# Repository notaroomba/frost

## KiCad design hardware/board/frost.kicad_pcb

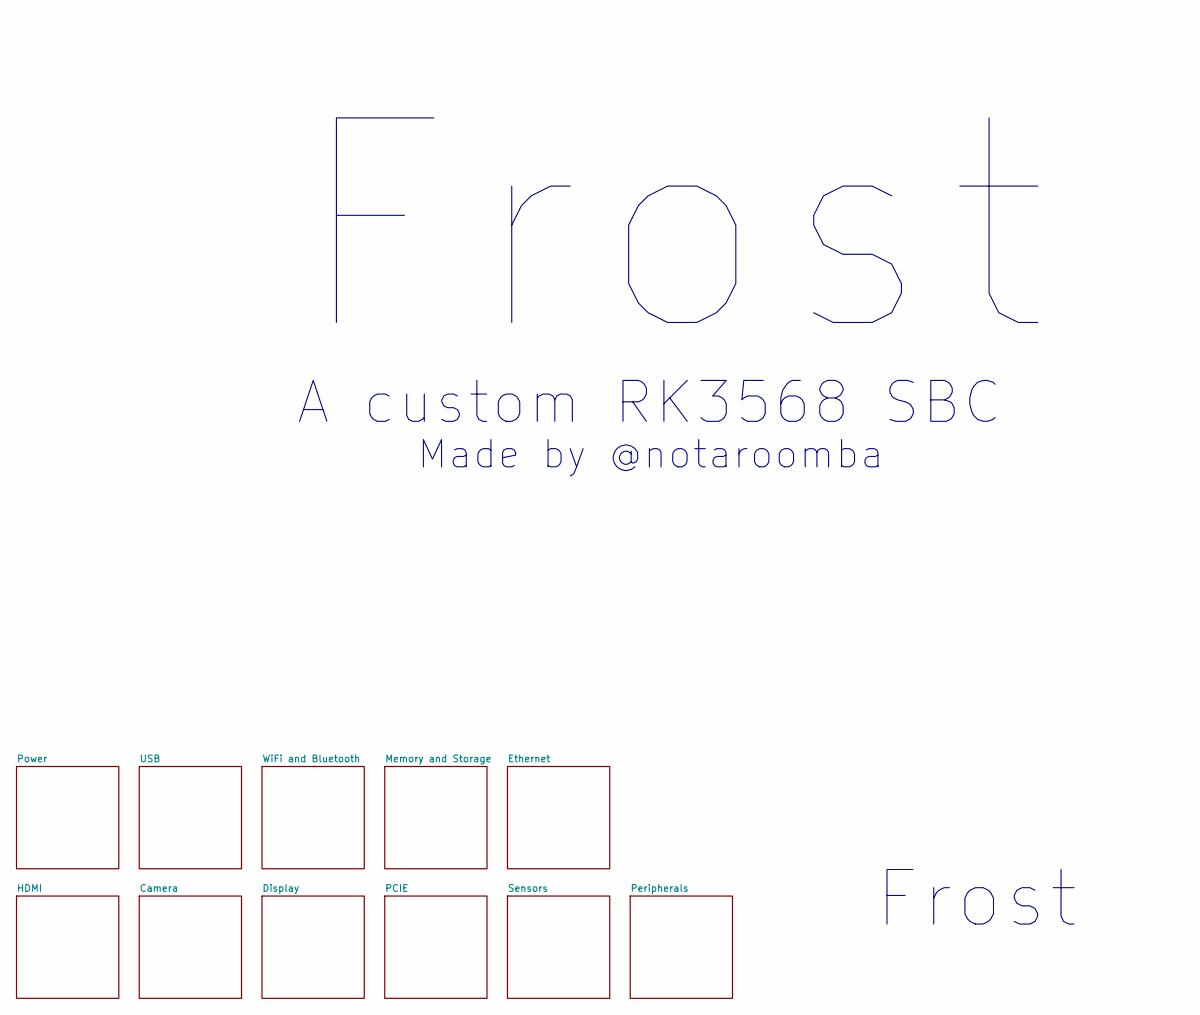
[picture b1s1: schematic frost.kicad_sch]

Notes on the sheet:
Frost
Made by @notaroomba
A custom RK3568 SBC

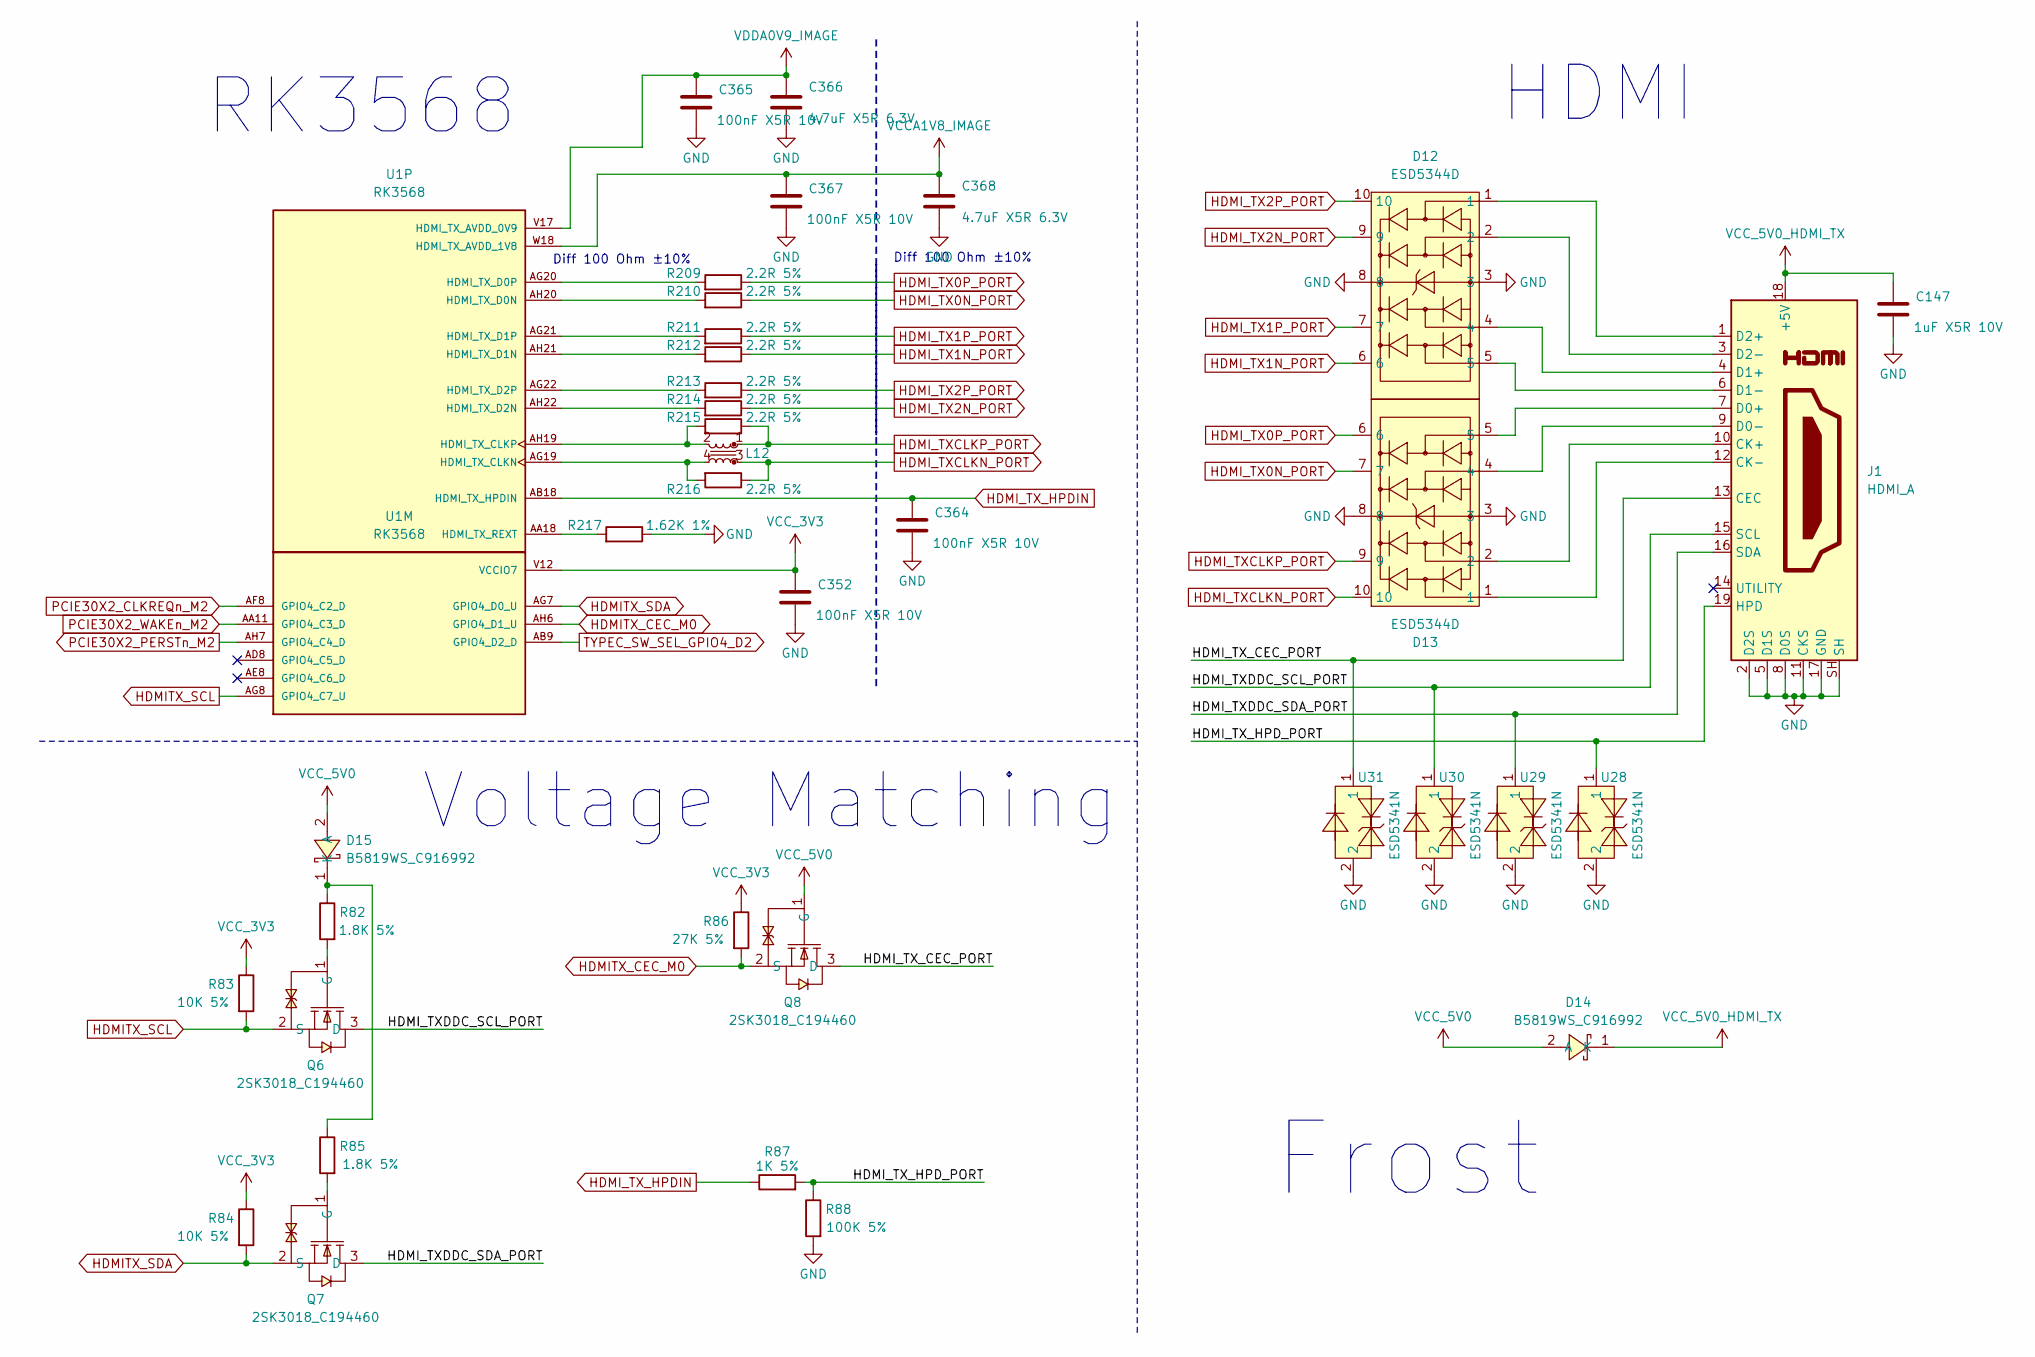
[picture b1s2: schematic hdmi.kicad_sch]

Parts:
C147: 1uF X5R 10V; C_0402_1005Metric
C352, C364, C365, C367: 100nF X5R 10V; C_0201_0603Metric
C366, C368: 4.7uF X5R 6.3V; C_0402_1005Metric
D12, D13: ESD5344D; DFN2510-10_L2.5-W1.0-P0.50-BL; LCSC Part C6562203
D14, D15: B5819WS_C916992; SOD-323_L1.7-W1.3-LS2.5-RD; LCSC Part C916992
J1: HDMI_A; HDMI_A_Amphenol_10029449-x01xLF_Horizontal
L12: L_Iron_Coupled_Small; FILTER-SMD_4P-L2.0-W1.2-BL_DLW21H
Q6, Q7, Q8: 2SK3018_C194460; SOT-323-3_L2.0-W1.3-P1.30-LS2.1-BR; LCSC Part C194460
R82, R85: 1.8K 5%; R_0402_1005Metric
R83, R84: 10K 5%; R_0402_1005Metric
R86: 27K 5%; R_0402_1005Metric
R87: 1K 5%; R_0402_1005Metric
R88: 100K 5%; R_0402_1005Metric
R209, R210, R211, R212, R213, R214, R215, R216: 2.2R 5%; R_0402_1005Metric
R217: 1.62K 1%; R_0201_0603Metric
U1: RK3568; BGA636C65P28X28_1900X1900X168; PARTREV 1.3; LCSC C3345225
U28, U29, U30, U31: ESD5341N; DFN1006-2L-RD; LCSC Part C3021106

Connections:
/HDMI/HDMI_TXDDC_SCL_PORT: J1.15 (SCL), Q6.3 (D), U30.1
/HDMI/HDMI_TXDDC_SDA_PORT: J1.16 (SDA), Q7.3 (D), U29.1
/HDMI/HDMI_TX_CEC_PORT: J1.13 (CEC), Q8.3 (D), U31.1
/HDMI/HDMI_TX_HPD_PORT: J1.19 (HPD), R87.2, R88.1, U28.1
HDMITX_CEC_M0: Q8.2 (S), R86.2, U1.AH6 (GPIO4_D1_U)
HDMITX_SCL: Q6.2 (S), R83.2, U1.AG8 (GPIO4_C7_U)
HDMITX_SDA: Q7.2 (S), R84.2, U1.AG7 (GPIO4_D0_U)
HDMI_TX0N_PORT: D13.7, R210.1
HDMI_TX0P_PORT: D13.6, R209.1
HDMI_TX1N_PORT: D12.6, R212.1
HDMI_TX1P_PORT: D12.7, R211.1
HDMI_TX2N_PORT: D12.9, R214.1
HDMI_TX2P_PORT: D12.10, R213.1
HDMI_TXCLKN_PORT: D13.10, L12.3, R216.1
HDMI_TXCLKP_PORT: D13.9, L12.1, R215.1
HDMI_TX_HPDIN: C364.1, R87.1, U1.AB18 (HDMI_TX_HPDIN)
unnamed: D15.1 (K), R82.1, R85.1
unnamed: D13.2, J1.10 (CK+)
unnamed: D13.1, J1.12 (CK-)
unnamed: D13.5, J1.7 (D0+)
unnamed: D13.4, J1.9 (D0-)
unnamed: D12.4, J1.4 (D1+)
unnamed: D12.5, J1.6 (D1-)
unnamed: D12.1, J1.1 (D2+)
unnamed: D12.2, J1.3 (D2-)
unnamed: Q6.1 (G), R82.2
unnamed: Q7.1 (G), R85.2
unnamed: L12.4, R216.2, U1.AG19 (HDMI_TX_CLKN)
unnamed: L12.2, R215.2, U1.AH19 (HDMI_TX_CLKP)
unnamed: R210.2, U1.AH20 (HDMI_TX_D0N)
unnamed: R209.2, U1.AG20 (HDMI_TX_D0P)
unnamed: R212.2, U1.AH21 (HDMI_TX_D1N)
unnamed: R211.2, U1.AG21 (HDMI_TX_D1P)
unnamed: R214.2, U1.AH22 (HDMI_TX_D2N)
unnamed: R213.2, U1.AG22 (HDMI_TX_D2P)
unnamed: R217.2, U1.AA18 (HDMI_TX_REXT)
PCIE30X2_CLKREQn_M2: U1.AF8 (GPIO4_C2_D); also elsewhere on the board
PCIE30X2_PERSTn_M2: U1.AH7 (GPIO4_C4_D); also elsewhere on the board
PCIE30X2_WAKEn_M2: U1.AA11 (GPIO4_C3_D); also elsewhere on the board
TYPEC_SW_SEL_GPIO4_D2: U1.AB9 (GPIO4_D2_D); also elsewhere on the board
VCCA1V8_IMAGE: C367.1, C368.1, U1.W18 (HDMI_TX_AVDD_1V8); also elsewhere on the board
VCC_3V3: C352.1, R83.1, R84.1, R86.1, U1.V12 (VCCIO7); also elsewhere on the board
VCC_5V0: D14.2 (A), D15.2 (A), Q8.1 (G); also elsewhere on the board
VCC_5V0_HDMI_TX: C147.1, D14.1 (K), J1.18 (+5V)
VDDA0V9_IMAGE: C365.1, C366.1, U1.V17 (HDMI_TX_AVDD_0V9), U1.V18 (HDMI_TX_AVDD_0V9); also elsewhere on the board

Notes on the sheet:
HDMI
RK3568
Voltage Matching
Frost
Diff 100 Ohm ±10%

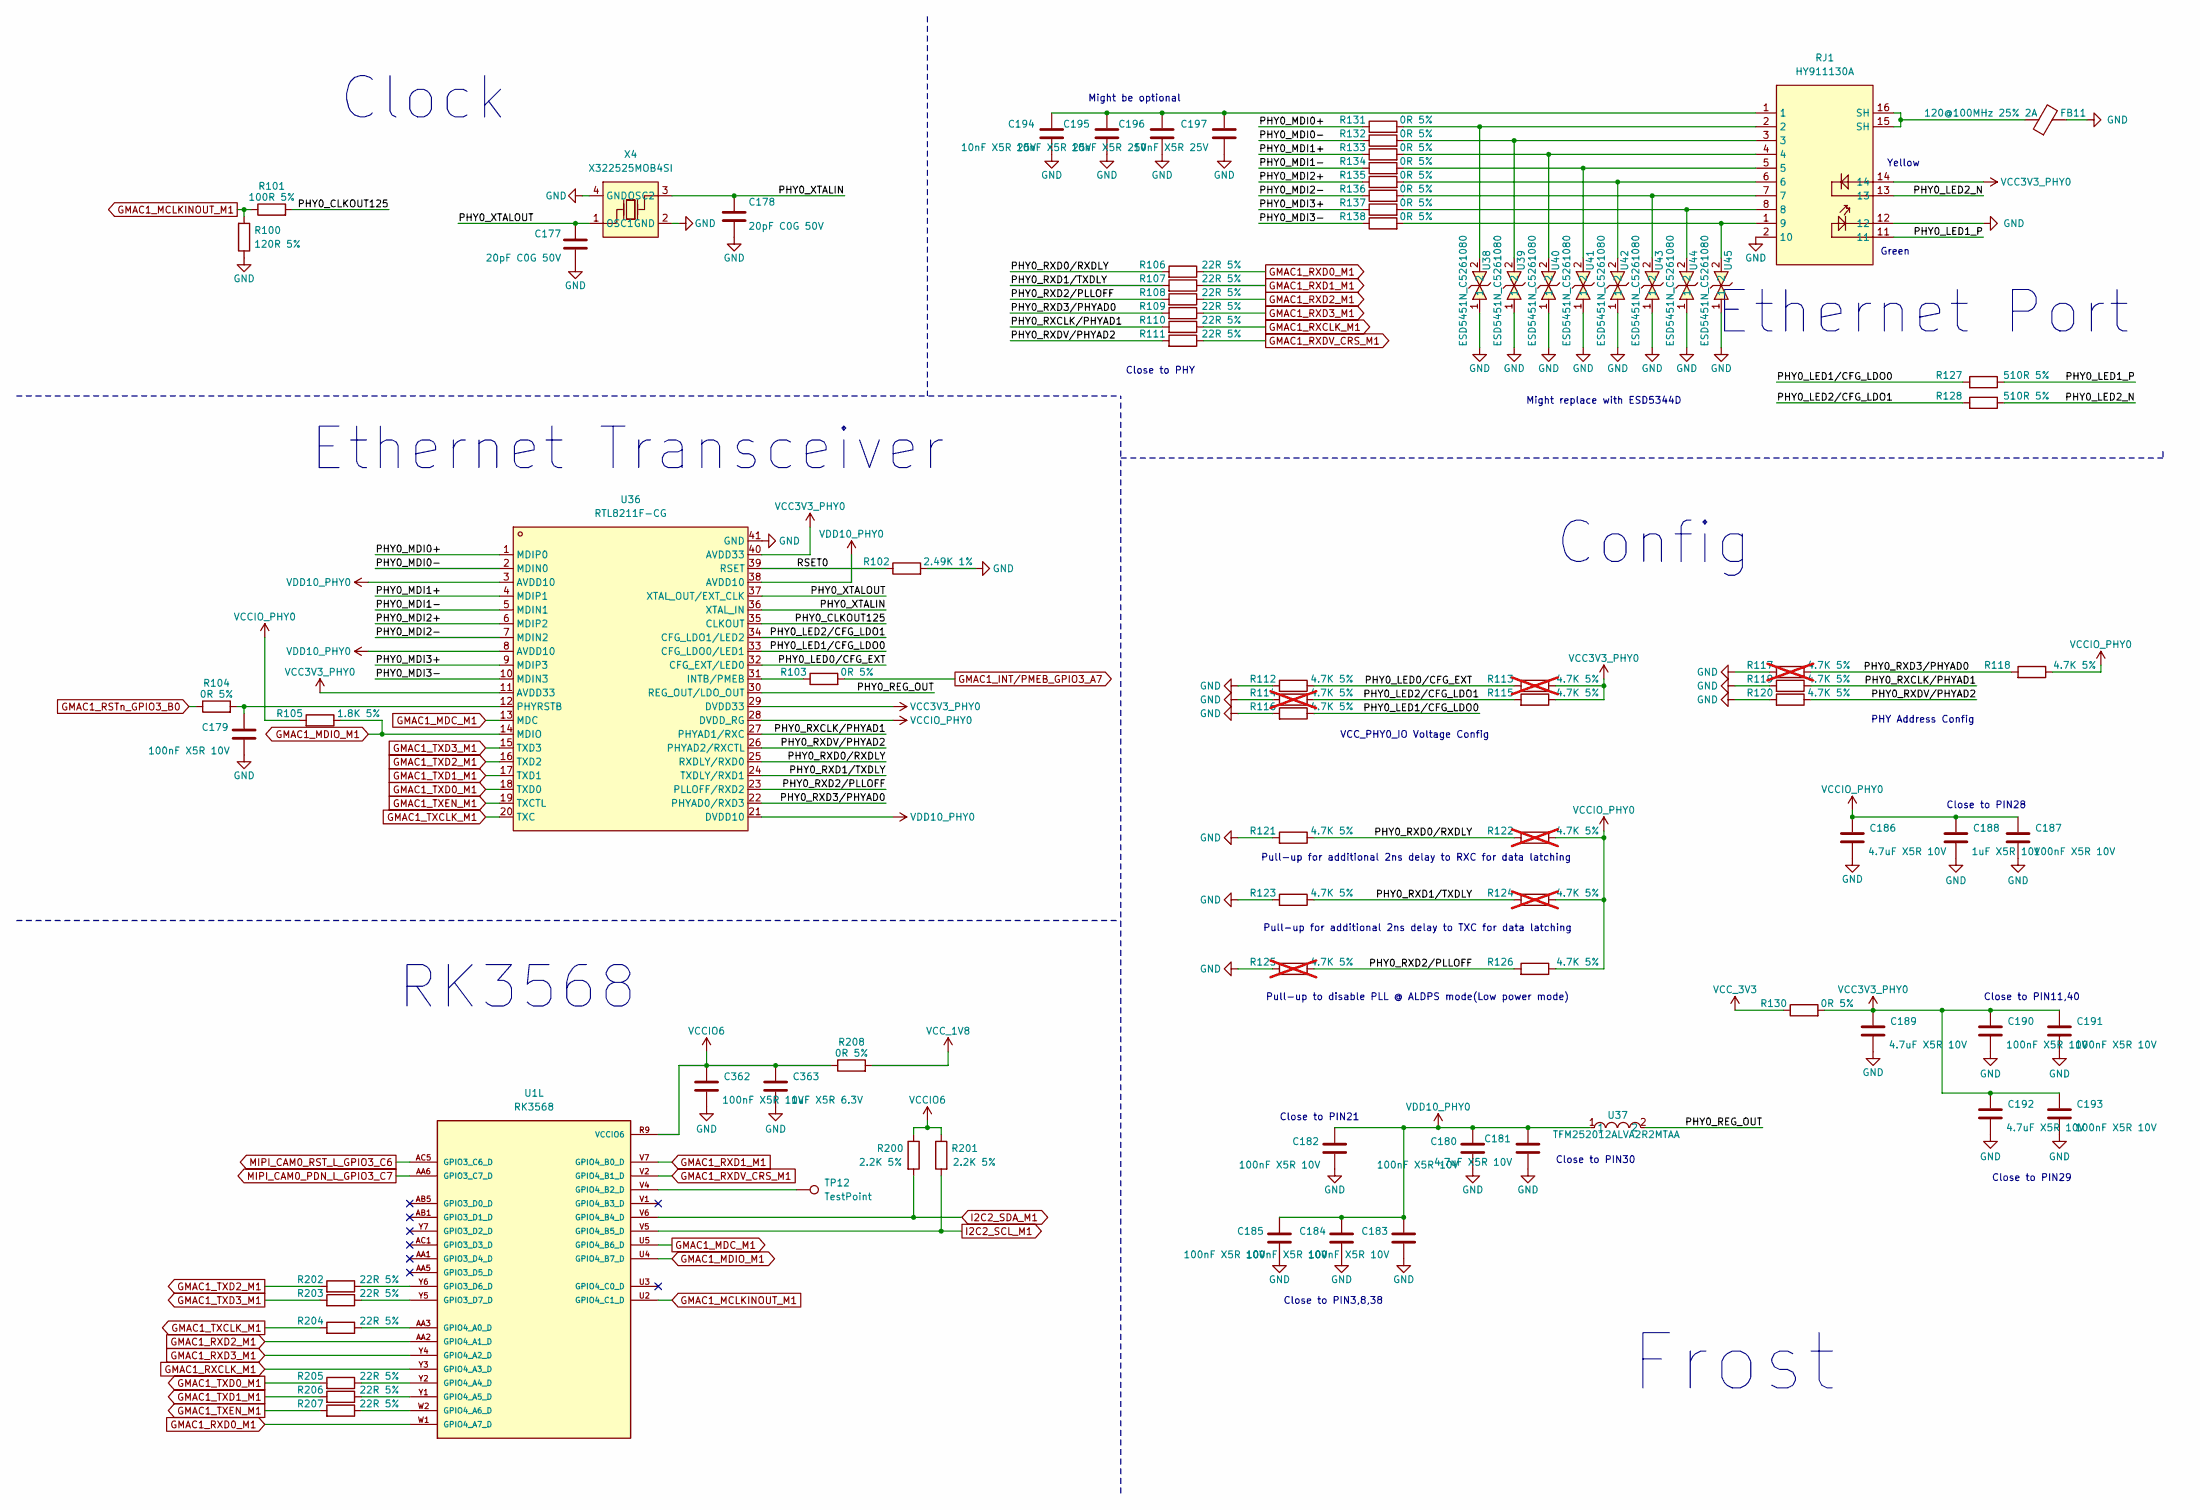
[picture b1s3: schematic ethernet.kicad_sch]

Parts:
C177, C178: 20pF C0G 50V; C_0402_1005Metric
C179, C180, C182, C183, C184, C185, C187, C190, C191, C193: 100nF X5R 10V; C_0402_1005Metric
C181, C186, C189, C192: 4.7uF X5R 10V; C_0603_1608Metric
C188: 1uF X5R 10V; C_0402_1005Metric
C194, C195, C196, C197: 10nF X5R 25V; C_0402_1005Metric
C362: 100nF X5R 10V; C_0201_0603Metric
C363: 1uF X5R 6.3V; C_0402_1005Metric
FB11: 120@100MHz 25% 2A; L_0603_1608Metric; LCSC C14709
R100: 120R 5%; R_0402_1005Metric
R101: 100R 5%; R_0402_1005Metric
R102: 2.49K 1%; R_0402_1005Metric
R103, R104, R130, R131, R132, R133, R134, R135, R136, R137, R138, R208: 0R 5%; R_0402_1005Metric
R105: 1.8K 5%; R_0402_1005Metric
R106, R107, R108, R109, R110, R111, R202, R203, R204, R205, R206, R207: 22R 5%; R_0402_1005Metric
R112, R115, R116, R118, R119, R120, R121, R123, R126: 4.7K 5%; R_0402_1005Metric
R113, R114, R117, R122, R124, R125: 4.7K 5%; R_0402_1005Metric; not fitted
R127, R128: 510R 5%; R_0402_1005Metric
R200, R201: 2.2K 5%; R_0402_1005Metric
RJ1: HY911130A; RJ45-TH_10P-P2.54-S2.54_L16.1-W21.4_HY911130A; LCSC Part C55679
TP12: TestPoint; TestPoint_Pad_D1.0mm
U1: RK3568; BGA636C65P28X28_1900X1900X168; PARTREV 1.3; LCSC C3345225
U36: RTL8211F-CG; WQFN-40_L5.0-W5.0-P0.4-BL-EP; LCSC Part C187932
U37: TFM252012ALVA2R2MTAA; L1008; LCSC Part C2047711
U38, U39, U40, U41, U42, U43, U44, U45: ESD5451N_C5261080; DFN1006-2L-BI; LCSC Part C5261080
X4: X322525MOB4SI; CRYSTAL-SMD_4P-L3.2-W2.5-BL; LCSC Part C9006

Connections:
/Ethernet/PHY0_CLKOUT125: R101.2, U36.35 (CLKOUT)
/Ethernet/PHY0_LED0/CFG_EXT: R112.1, R113.2, U36.32 (CFG_EXT/LED0)
/Ethernet/PHY0_LED1_P: R127.1, RJ1.11
/Ethernet/PHY0_LED1/CFG_LDO0: R116.1, R127.2, U36.33 (CFG_LDO0/LED1)
/Ethernet/PHY0_LED2_N: R128.1, RJ1.13
/Ethernet/PHY0_LED2/CFG_LDO1: R114.1, R115.2, R128.2, U36.34 (CFG_LDO1/LED2)
/Ethernet/PHY0_MDI0+: R131.1, U36.1 (MDIP0)
/Ethernet/PHY0_MDI0-: R132.1, U36.2 (MDIN0)
/Ethernet/PHY0_MDI1+: R133.1, U36.4 (MDIP1)
/Ethernet/PHY0_MDI1-: R134.1, U36.5 (MDIN1)
/Ethernet/PHY0_MDI2+: R135.1, U36.6 (MDIP2)
/Ethernet/PHY0_MDI2-: R136.1, U36.7 (MDIN2)
/Ethernet/PHY0_MDI3+: R137.1, U36.9 (MDIP3)
/Ethernet/PHY0_MDI3-: R138.1, U36.10 (MDIN3)
/Ethernet/PHY0_REG_OUT: U36.30 (REG_OUT/LDO_OUT), U37.2
/Ethernet/PHY0_RXCLK/PHYAD1: R110.2, R119.1, U36.27 (PHYAD1/RXC)
/Ethernet/PHY0_RXD0/RXDLY: R106.2, R121.1, R122.2, U36.25 (RXDLY/RXD0)
/Ethernet/PHY0_RXD1/TXDLY: R107.2, R123.1, R124.2, U36.24 (TXDLY/RXD1)
/Ethernet/PHY0_RXD2/PLLOFF: R108.2, R125.1, R126.2, U36.23 (PLLOFF/RXD2)
/Ethernet/PHY0_RXD3/PHYAD0: R109.2, R117.1, R118.2, U36.22 (PHYAD0/RXD3)
/Ethernet/PHY0_RXDV/PHYAD2: R111.2, R120.1, U36.26 (PHYAD2/RXCTL)
/Ethernet/PHY0_XTALIN: C178.1, U36.36 (XTAL_IN), X4.3 (OSC2)
/Ethernet/PHY0_XTALOUT: C177.1, U36.37 (XTAL_OUT/EXT_CLK), X4.1 (OSC1)
/Ethernet/RSET0: R102.1, U36.39 (RSET)
GMAC1_INT/PMEB_GPIO3_A7: R103.2
GMAC1_MCLKINOUT_M1: R100.2, R101.1, U1.U2 (GPIO4_C1_D)
GMAC1_MDC_M1: U1.U5 (GPIO4_B6_D), U36.13 (MDC)
GMAC1_MDIO_M1: R105.1, U1.U4 (GPIO4_B7_D), U36.14 (MDIO)
GMAC1_RSTn_GPIO3_B0: R104.1
GMAC1_RXCLK_M1: R110.1, U1.Y3 (GPIO4_A3_D)
GMAC1_RXD0_M1: R106.1, U1.W1 (GPIO4_A7_D)
GMAC1_RXD1_M1: R107.1, U1.V7 (GPIO4_B0_D)
GMAC1_RXD2_M1: R108.1, U1.AA2 (GPIO4_A1_D)
GMAC1_RXD3_M1: R109.1, U1.Y4 (GPIO4_A2_D)
GMAC1_RXDV_CRS_M1: R111.1, U1.V2 (GPIO4_B1_D)
GMAC1_TXCLK_M1: R204.2, U36.20 (TXC)
GMAC1_TXD0_M1: R205.2, U36.18 (TXD0)
GMAC1_TXD1_M1: R206.2, U36.17 (TXD1)
GMAC1_TXD2_M1: R202.2, U36.16 (TXD2)
GMAC1_TXD3_M1: R203.2, U36.15 (TXD3)
GMAC1_TXEN_M1: R207.2, U36.19 (TXCTL)
I2C2_SCL_M1: R201.2, U1.V5 (GPIO4_B5_D); also elsewhere on the board
I2C2_SDA_M1: R200.2, U1.V6 (GPIO4_B4_D); also elsewhere on the board
MIPI_CAM0_PDN_L_GPIO3_C7: U1.AA6 (GPIO3_C7_D)
MIPI_CAM0_RST_L_GPIO3_C6: U1.AC5 (GPIO3_C6_D); also elsewhere on the board
unnamed: FB11.1, RJ1.15 (SH), RJ1.16 (SH)
unnamed: R132.2, RJ1.3, U39.2
unnamed: R133.2, RJ1.4, U40.2
unnamed: R134.2, RJ1.5, U41.2
unnamed: R135.2, RJ1.6, U42.2
unnamed: R136.2, RJ1.7, U43.2
unnamed: R137.2, RJ1.8, U44.2
unnamed: R202.1, U1.Y6 (GPIO3_D6_D)
unnamed: R203.1, U1.Y5 (GPIO3_D7_D)
unnamed: R204.1, U1.AA3 (GPIO4_A0_D)
unnamed: R205.1, U1.Y2 (GPIO4_A4_D)
unnamed: R206.1, U1.Y1 (GPIO4_A5_D)
unnamed: R207.1, U1.W2 (GPIO4_A6_D)
unnamed: TP12.1, U1.V4 (GPIO4_B2_D)
unnamed: R103.1, U36.31 (INTB/PMEB)
unnamed: C179.1, R104.2, U36.12 (PHYRSTB)
VCC3V3_PHY0: C189.1, C190.1, C191.1, C192.1, C193.1, R113.1, R115.1, R130.2, RJ1.14, U36.11 (AVDD33), U36.29 (DVDD33), U36.40 (AVDD33)
VCCIO6: C362.1, C363.1, R200.1, R201.1, R208.1, U1.R9 (VCCIO6), U1.U9 (VCCIO6)
VCCIO_PHY0: C186.1, C187.1, C188.1, R105.2, R118.1, R122.1, R124.1, R126.1, U36.28 (DVDD_RG)
VCC_1V8: R208.2; also elsewhere on the board
VCC_3V3: R130.1; also elsewhere on the board
VDD10_PHY0: C180.1, C181.1, C182.1, C183.1, C184.1, C185.1, U36.3 (AVDD10), U36.8 (AVDD10), U36.21 (DVDD10), U36.38 (AVDD10), U37.1

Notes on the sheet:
Close to PIN29
Might replace with ESD5344D
Config
Might be optional
Close to PHY
Close to PIN30
Green
Ethernet Port
Pull-up to disable PLL @ ALDPS mode(Low power mode)
Pull-up for additional 2ns delay to TXC for data latching
Frost
Yellow
Close to PIN21
Clock
Pull-up for additional 2ns delay to RXC for data latching
Close to PIN28
RK3568
Close to PIN11,40
Ethernet Transceiver
PHY Address Config
Close to PIN3,8,38
VCC_PHY0_IO Voltage Config
